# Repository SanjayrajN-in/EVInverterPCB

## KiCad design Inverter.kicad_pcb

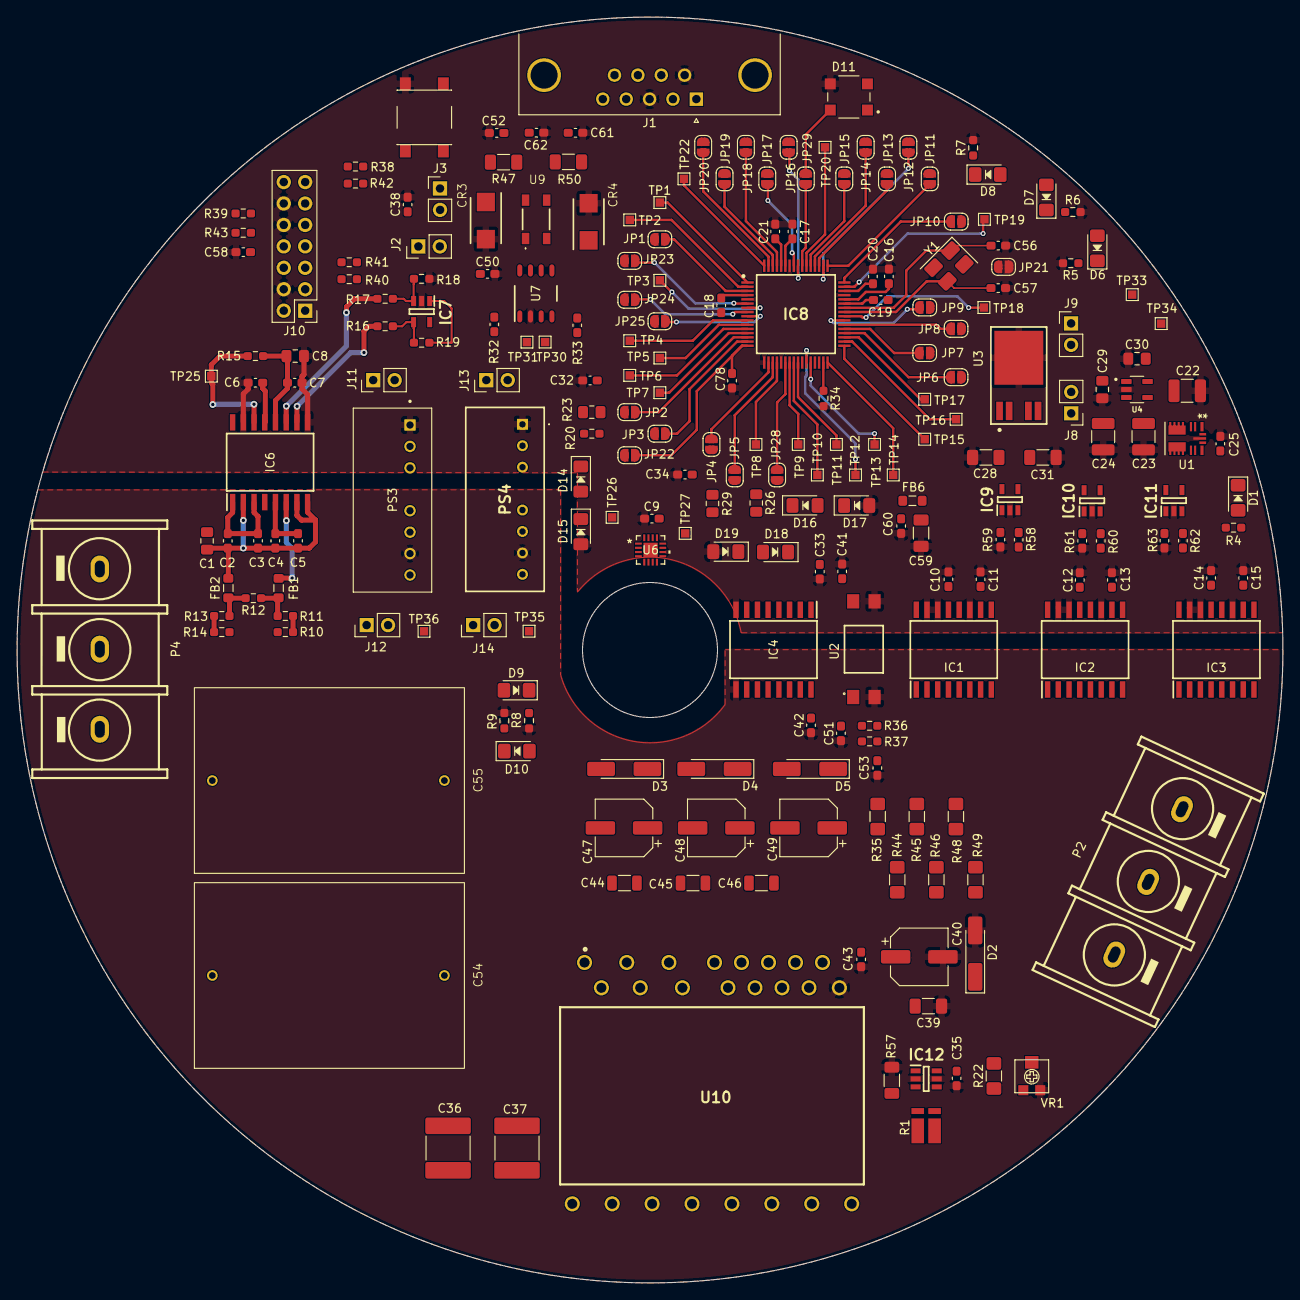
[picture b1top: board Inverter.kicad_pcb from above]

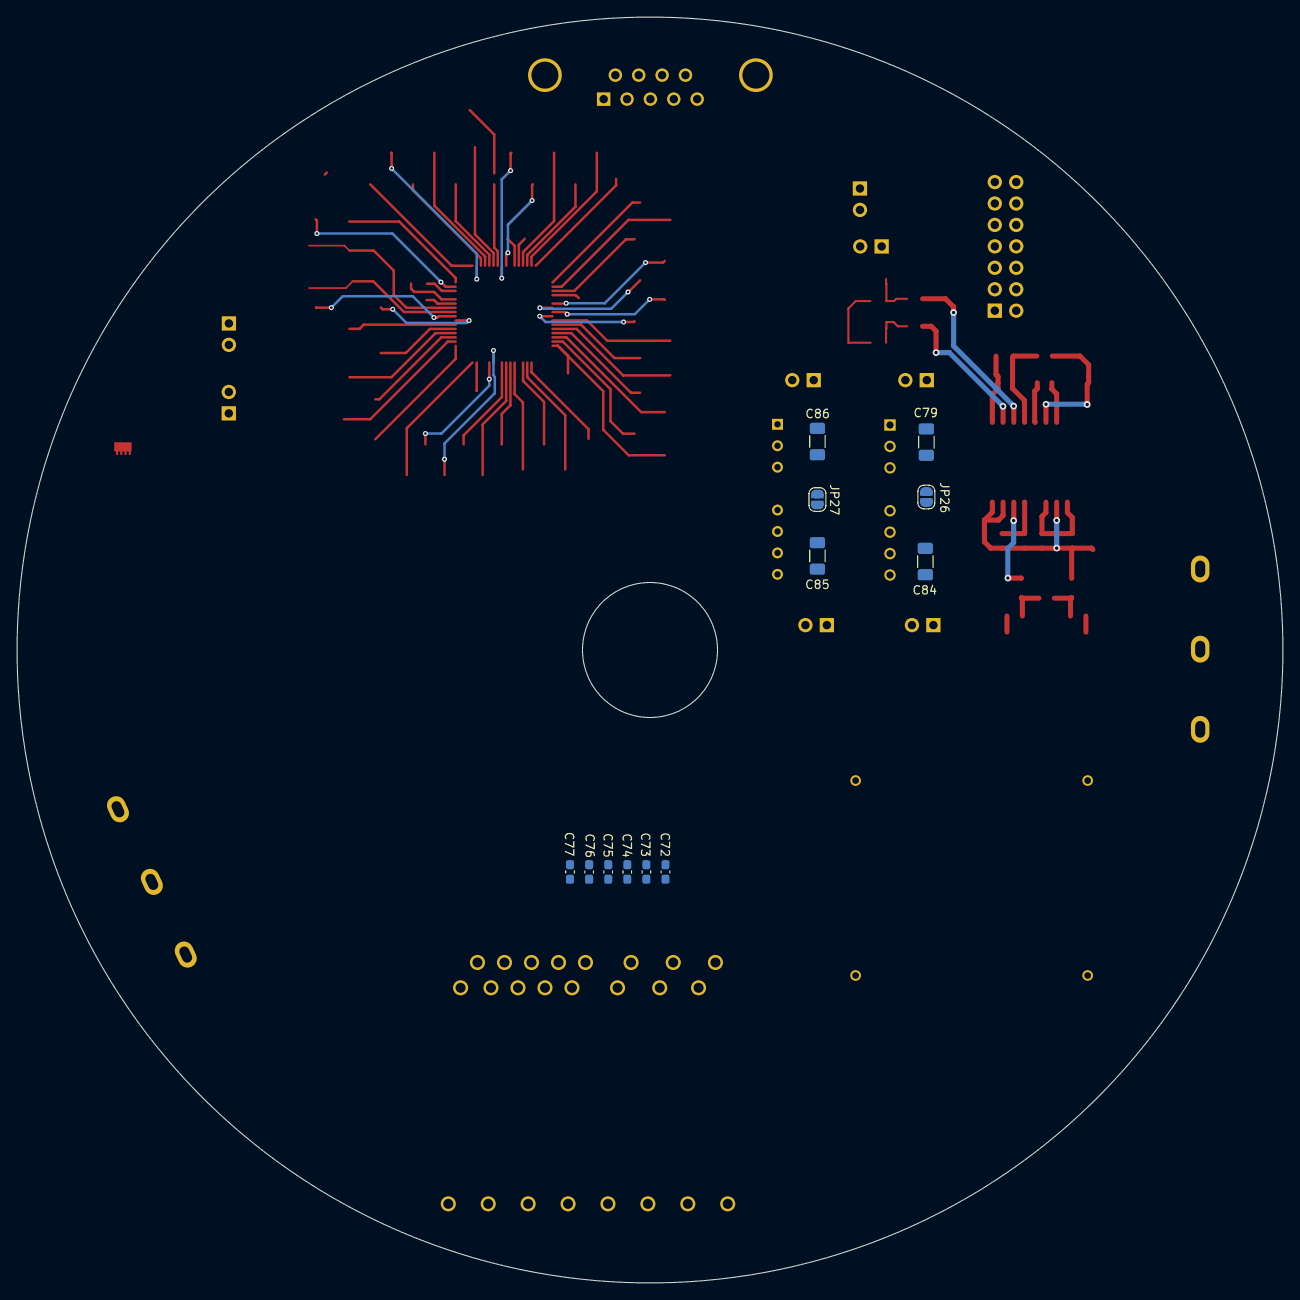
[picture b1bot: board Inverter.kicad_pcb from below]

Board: 2 copper layers, 150.0 x 150.0 mm, 236 parts (12 on the bottom side), 176 nets.

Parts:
C1, C8: 1u; C_0805_2012Metric_Pad1.18x1.45mm_HandSolder
C2, C5, C7: 1n; C_0603_1608Metric_Pad1.08x0.95mm_HandSolder
C3, C4, C6, C16, C17, C18, C19, C20, C21, C58, C60: 100n; C_0603_1608Metric_Pad1.08x0.95mm_HandSolder
C9, C25, C35: 1uF; C_0603_1608Metric_Pad1.08x0.95mm_HandSolder
C10, C12, C14, C43, C53: 1nF; C_0603_1608Metric_Pad1.08x0.95mm_HandSolder
C11, C41, C42, C51: 0.1uF; C_0603_1608Metric_Pad1.08x0.95mm_HandSolder
C13, C15, C38, C50, C52, C61, C62: 0.1u; C_0603_1608Metric_Pad1.08x0.95mm_HandSolder
C22: 4.7uF; C_1210_3225Metric_Pad1.33x2.70mm_HandSolder
C23, C24: 22uF; C_1210_3225Metric_Pad1.33x2.70mm_HandSolder
C28, C31, C84: 10uF; C_1206_3216Metric_Pad1.33x1.80mm_HandSolder
C29, C30: 10uF; C_0805_2012Metric_Pad1.18x1.45mm_HandSolder
C32, C33, C34, C72, C73, C74, C75, C76, C77: 100nF; C_0603_1608Metric_Pad1.08x0.95mm_HandSolder
C36, C37: 2.2u; C_2220_5750Metric_Pad1.97x5.40mm_HandSolder
C39: 1u; C_1206_3216Metric_Pad1.33x1.80mm_HandSolder
C40: 10u; CP_Elec_6.3x5.9
C44, C45, C46: 2.2uF; C_1206_3216Metric
C47, C48, C49: 100uF/25V; CP_Elec_6.3x5.9
C54, C55: 22u; FilmCap
C56, C57: 22pF; C_0603_1608Metric_Pad1.08x0.95mm_HandSolder
C59: 4.7u; C_1206_3216Metric_Pad1.33x1.80mm_HandSolder
C78: 2.2uF; C_0603_1608Metric_Pad1.08x0.95mm_HandSolder
C79, C85, C86: 47uF; C_1206_3216Metric_Pad1.33x1.80mm_HandSolder
CR3, CR4: SMBJ30CA; DIOM5436X244N
D1: RED_LED; LED_1206
D2, D3, D4, D5: 16V; D_MiniMELF_Handsoldering
D6, D7, D8, D9, D10: LED; LED_1206
D11: XL-5050RGBC-WS2812B; LED_XL-5050RGBC-WS2812B
D14, D15, D16, D17, D18, D19: D_Zener; D_1206
FB1, FB2, FB6: FerriteBead; L_0805_2012Metric_Pad1.05x1.20mm_HandSolder
IC1, IC2, IC3: ACS724LMATR-20AB-T; SOIC127P1030X265-16N
IC4: ISO7760FQDWQ1; SOIC127P1030X265-16N
IC6: AMC3311QDWERQ1; SOIC127P1030X265-16N
IC7, IC9, IC10, IC11: OPA388QDBVRQ1; SOT95P280X145-5N
IC8: F2800157QPMQ1; QFP50P1200X1200X160-64N
IC12: INA181A2QDBVRQ1; SOT95P280X145-6N
J1: Conn_01x09_Pin; DSUB-9_Pins_Horizontal_P2.77x2.84mm_EdgePinOffset4.94mm_Hou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
J2, J3, J8, J9, J11, J12, J13, J14: Conn_01x02_Pin; PinHeader_1x02_P2.54mm_Vertical
J10: Conn_02x07_Odd_Even; PinHeader_2x07_P2.54mm_Vertical
JP1, JP2, JP3, JP4, JP5, JP6, JP7, JP8, JP9, JP10, JP11, JP12, JP13, JP14, JP15, JP16, JP17, JP18, JP19, JP20, JP21, JP22, JP23, JP24, JP25, JP26, JP27, JP28, JP29: SolderJumper_2_Open; SolderJumper-2_P1.3mm_Open_RoundedPad1.0x1.5mm
P2, P4: WJ45C-B-3P
PS3: MCWI05-12S05; CONV_MCWI05-12S05
PS4: MCWI05-12S15; MCWI0512S15
R1: 0.0007; WSK1216
R4, R12, R34, R37, R38, R39, R40, R41, R42, R43: 10k; R_0603_1608Metric_Pad0.98x0.95mm_HandSolder
R5, R6, R7, R8, R9: 2.2k; R_0603_1608Metric_Pad0.98x0.95mm_HandSolder
R10, R14, R16, R17, R18, R19: 100k; R_0603_1608Metric_Pad0.98x0.95mm_HandSolder
R11, R13: 150k; R_0603_1608Metric_Pad0.98x0.95mm_HandSolder
R15: 47k; R_0603_1608Metric_Pad0.98x0.95mm_HandSolder
R20: 100; R_0603_1608Metric_Pad0.98x0.95mm_HandSolder
R22, R35, R44, R45, R46, R48, R49: R; R_1206
R23, R26, R29: 100; C_0805_2012Metric_Pad1.18x1.45mm_HandSolder
R32, R33: 50; C_0603_1608Metric_Pad1.08x0.95mm_HandSolder
R36: 220; R_0603_1608Metric_Pad0.98x0.95mm_HandSolder
R47, R50: 60; C_1206_3216Metric_Pad1.33x1.80mm_HandSolder
R57: 0R; R_1206_3216Metric_Pad1.30x1.75mm_HandSolder
R58, R60, R62: 10k; C_0603_1608Metric_Pad1.08x0.95mm_HandSolder
R59, R61, R63: 19.6k; C_0603_1608Metric_Pad1.08x0.95mm_HandSolder
SW1: SW_MEC_5E; PushButton
TP1, TP2, TP3, TP4, TP5, TP6, TP7, TP8, TP9, TP10, TP11, TP12, TP13, TP14, TP15, TP16, TP17, TP18, TP19, TP20, TP22, TP25, TP26, TP27, TP30, TP31, TP33, TP34, TP35, TP36: TestPoint; TestPoint_Pad_1.0x1.0mm
U1: TPSM33610S5QRDNRQ1
U2: VO617A-3X018T; SOIC254P1210X390-4N
U3: TPS78533QKVURQ1; TO114P998X235-6_5N-V
U4: TLV70012QDDCRQ1; SOT95P280X110-5N
U6: MA732GQ-P; QFN-16_MA732
U7: TCAN1042HGVDRQ1; D0008A_N
U9: ACT45C-110-2P-TL000
U10: IGCM15F60GA
VR1: EVM-3YSX50B53
Y1: Crystal_GND24; Crystal_SMD_EuroQuartz_MT-4Pin_3.2x2.5mm_HandSoldering

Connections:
+1V2: C16.1, C17.1, C18.1, D8.2 (A), IC8.4 (VDD_1), IC8.44 (VDD_2), IC8.59 (VDD_3), J9.1, TP33.1 (1_1)
+3.3V: C9.1, C19.1, C20.1, C21.1, C41.2, D7.2 (A), FB6.1, IC4.1 (VCC1), IC7.5 (V+), IC8.43 (VDDIO_1), IC8.46 (VREGENZ), IC8.60 (VDDIO_2), J3.1, J8.2, J10.5, R38.1, R39.1, R40.1, R41.1, R42.1, R43.2, TP34.1 (1_1), U6.13 (VDD)
+5V: C7.2, C8.2, C11.1, C13.1, C15.1, C23.1, C24.1, C28.2, D6.2 (A), D11.1 (VDD), IC1.10 (VCC), IC2.10 (VCC), IC3.10 (VCC), IC6.12 (VDD), J2.1, R15.1, U1.4 (VOUT), U1.9 (FB), U3.1 (EN), U3.2 (IN)
+5VA: C35.1, C42.2, D10.2 (A), IC4.16 (VCC2), IC12.6 (VS), J12.2, R37.1, TP36.1 (1_1)
+12V: C22.1, J1.9, J11.1, J13.1, R4.1, U1.2 (EN), U1.3 (VIN)
+15V: C39.1, C40.1, D2.1 (K), D9.2 (A), J14.2, TP35.1 (1_1), U10.13 (VDD)
+DCLink: C36.2, C37.1, C54.2, C55.1, P4.1, R10.1, U10.23
+INSense: IC12.3 (IN+), R1.3
-DCLink: C36.1, C37.2, C54.1, C55.2, P4.3, R1.1, R14.2, R57.1
-INSense: IC12.4 (IN-), R1.2
/Interface/VCC: C50.1, J2.2, U7.3 (VCC)
/Interface/VIO: C38.1, J3.2, U7.5 (VIO)
/Inverter_PowerStage/A: C72.1, R35.2, U10.7 (HIN(U))
/Inverter_PowerStage/B: C73.1, R44.2, U10.8 (HIN(V))
/Inverter_PowerStage/C: C74.1, R45.2, U10.9 (HIN(W))
/Inverter_PowerStage/D: C75.1, R46.2, U10.10 (LIN(U))
/Inverter_PowerStage/E: C76.1, R48.2, U10.11 (LIN(V))
/Inverter_PowerStage/F: C77.1, R49.2, U10.12 (LIN(W))
/Power_SM/PGOOD: D1.1 (K), U1.1 (PGOOD)
ADC_IU: C32.1, D14.2 (A), D15.1 (K), JP2.2 (B), R23.1
ADC_IV: C33.1, D16.2 (A), D17.1 (K), JP5.2 (B), R26.1
ADC_IW: C34.1, D18.2 (A), D19.1 (K), JP4.2 (B), R29.1
AD_REF: C59.1, C60.1, D14.1 (K), D16.1 (K), D18.1 (K), FB6.2, IC9.5 (V+), IC10.5 (V+), IC11.5 (V+), JP22.2 (B), JP28.2 (B)
CAN1RX: R33.2, TP30.1 (1_1), U7.4 (RXD)
CAN1TX: R32.2, TP31.1 (1_1), U7.1 (TXD)
CANH: C52.1, J1.7, R47.1, U9.4
CANL: C61.2, J1.2, R50.2, U9.3
CANSTB: IC8.31 (GPIO11), R34.1, U7.8 (STB)
DC_OUTN: IC6.10 (OUTN), R16.2
DC_OUTP: IC6.11 (OUTP), R17.2
DC_Sense: JP3.2 (B), R20.2
DIN_LED: D11.4 (DIN), JP29.1 (A)
EMU0: J10.13, R38.2
EMU1: J10.14, R39.2
GND: C6.2, C7.1, C8.1, C9.2, C10.2, C11.2, C12.2, C13.2, C14.2, C15.2, C16.2, C17.2, C18.2, C19.2, C20.2, C21.2, C22.2, C23.2, C24.2, C25.2, C28.1, C29.1, C30.1, C31.2, C32.2, C33.2, C34.2, C38.2, C41.1, C50.2, C52.2, C56.2, C57.1, C58.2, C59.2, C60.2, C61.1, C62.2, C78.2, C79.2, C86.1, CR3.2, CR4.2, D11.3 (GND), D15.2 (A), D17.2 (A), D19.2 (A), IC1.11 (NC_2), IC1.14 (NC_3), IC1.15 (GND), IC2.11 (NC_2), IC2.14 (NC_3), IC2.15 (GND), IC3.11 (NC_2), IC3.14 (NC_3), IC3.15 (GND), IC4.8 (GND1), IC6.9 (GND), IC6.15 (DCDC_GND), IC7.2 (V-), IC8.5 (VSS_1), IC8.17 (VREFLO), IC8.21 (VSSA), IC8.26 (VSS_2), IC8.45 (VSS_3), IC8.58 (VSS_4), IC9.2 (V-), IC10.2 (V-), IC11.2 (V-), J1.3, J1.6, J10.4, J10.10, J10.12, JP21.1 (A), JP26.2 (B), JP27.2 (B), PS3.1 (-VIN), PS4.1 (-VIN), R5.2, R6.2, R7.2, R18.2, R34.2, R59.2, R61.2, R63.2, SW1.2, U1.10 (GND), U1.11 (MODE/SYNC), U2.3, U3.3 (GND), U4.2 (GND), U6.8 (GND), U6.10 (TEST), U6.17 (PAD), U7.2 (GND)
GND1: C35.2, C39.2, C40.2, C42.1, C43.2, C51.2, C53.2, C72.2, C73.2, C74.2, C75.2, C76.2, C77.2, C84.2, C85.2, D2.2 (A), IC4.9 (GND2), IC12.2 (GND), IC12.5 (REF), PS3.7 (-VOUT), PS4.7 (-VOUT), R8.2, R9.2, R57.2, U2.2, U10.16 (VSS), VR1.P$3
ITRIP: C43.1, R22.2, U10.15 (ITRIP), VR1.P$1, VR1.P$2
ITRIPOUT: IC12.1 (OUT), R22.1
Iu_In: IC1.1 (IP+_1), IC1.2 (IP+_2), IC1.3 (IP+_3), IC1.4 (IP+_4), U10.22 (U)
Iu_Out: IC1.5 (IP-_1), IC1.6 (IP-_2), IC1.7 (IP-_3), IC1.8 (IP-_4), P2.1
Iu_div: IC9.3 (+IN), R58.2, R59.1
Iu_sense: IC1.12 (VIOUT), R58.1
Iv_In: IC2.1 (IP+_1), IC2.2 (IP+_2), IC2.3 (IP+_3), IC2.4 (IP+_4), U10.21 (V)
Iv_Out: IC2.5 (IP-_1), IC2.6 (IP-_2), IC2.7 (IP-_3), IC2.8 (IP-_4), P2.2
Iv_div: IC10.3 (+IN), R60.2, R61.1
Iv_sense: IC2.12 (VIOUT), R60.1
Iw_In: IC3.1 (IP+_1), IC3.2 (IP+_2), IC3.3 (IP+_3), IC3.4 (IP+_4), U10.20 (W)
Iw_Out: IC3.5 (IP-_1), IC3.6 (IP-_2), IC3.7 (IP-_3), IC3.8 (IP-_4), P2.3
Iw_div: IC11.3 (+IN), R62.2, R63.1
Iw_sense: IC3.12 (VIOUT), R62.1
JTAG_SEL: C58.1, J10.8, R43.1
unnamed: C62.1, R47.2, R50.1
unnamed: D1.2 (A), R4.2
unnamed: D6.1 (K), R5.1
unnamed: D7.1 (K), R6.1
unnamed: D8.1 (K), R7.1
unnamed: D9.1 (K), R8.1
unnamed: D10.1 (K), R9.1
unnamed: FB1.1, R11.2, R12.1
unnamed: FB2.1, R12.2, R13.1
unnamed: C10.1, IC1.13 (FILTER)
unnamed: C12.1, IC2.13 (FILTER)
unnamed: C14.1, IC3.13 (FILTER)
unnamed: IC4.15 (OUTA), R49.1
unnamed: IC4.14 (OUTB), R48.1
unnamed: IC4.13 (OUTC), R46.1
unnamed: IC4.12 (OUTD), R45.1
unnamed: IC4.11 (OUTE), R44.1
unnamed: IC4.10 (OUTF), R35.1
unnamed: C1.1, C2.1, C3.1, C4.1, C5.2, FB2.2, IC6.2 (DCDC_HGND), IC6.7 (HGND_1), IC6.8 (HGND_2)
unnamed: C6.1, IC6.13 (LDO_OUT), IC6.16 (DCDC_IN)
unnamed: C1.2, C2.2, C3.2, IC6.1 (DCDC_OUT), IC6.3 (HLDO_IN)
unnamed: IC6.14 (DIAG), R15.2, TP25.1 (1_1)
unnamed: C4.2, C5.1, IC6.5 (HLDO_OUT)
unnamed: FB1.2, IC6.6 (IN)
unnamed: IC7.3 (+IN), R17.1, R18.1
unnamed: IC7.4 (-IN), R16.1, R19.1
unnamed: IC7.1 (OUT), R19.2, R20.1
unnamed: IC8.15 (A0/C15/CMP1_DACL), JP3.1 (A)
unnamed: IC8.14 (A1), JP2.1 (A)
unnamed: IC8.9 (A2/C9GPIO224), JP25.2 (B)
unnamed: IC8.8 (A3/C5GPIO242), JP24.2 (B)
unnamed: IC8.23 (A4/C14), TP9.1 (1_1)
unnamed: IC8.13 (A5/C2), TP7.1 (1_1)
unnamed: IC8.6 (A6GPIO228), JP23.2 (B)
unnamed: IC8.19 (A7/C3), JP5.1 (A)
unnamed: IC8.20 (A8/C11), TP8.1 (1_1)
unnamed: IC8.25 (A10/C10GPIO230), TP11.1 (1_1)
unnamed: IC8.12 (A11/C0), TP6.1 (1_1)
unnamed: IC8.18 (A12/C1), JP4.1 (A)
unnamed: IC8.10 (A15/C7), TP4.1 (1_1)
unnamed: IC8.2 (A16/C16GPIO28), TP2.1 (1_1)
unnamed: IC8.27 (A17/C17GPIO20), TP12.1 (1_1)
unnamed: IC8.28 (A18/C18GPIO21), TP13.1 (1_1)
unnamed: IC8.29 (A19/C19GPIO13), R32.1
unnamed: IC8.30 (A20/C20GPIO12), R33.1
unnamed: IC8.11 (C4/A14), TP5.1 (1_1)
unnamed: IC8.7 (C6GPIO226), TP3.1 (1_1)
unnamed: IC8.24 (C8/A9GPIO227), TP10.1 (1_1)
unnamed: IC8.52 (GPIO0), JP14.2 (B)
unnamed: IC8.51 (GPIO1), JP13.2 (B)
unnamed: IC8.50 (GPIO2), JP12.2 (B)
unnamed: IC8.49 (GPIO3), JP11.2 (B)
unnamed: IC8.48 (GPIO4), JP10.1 (A)
unnamed: IC8.61 (GPIO5), JP18.2 (B)
unnamed: IC8.64 (GPIO6), TP22.1 (1_1)
unnamed: IC8.57 (GPIO7), JP17.2 (B)
unnamed: IC8.47 (GPIO8), TP19.1 (1_1)
unnamed: IC8.62 (GPIO9), JP19.2 (B)
unnamed: IC8.63 (GPIO10), JP20.2 (B)
unnamed: IC8.33 (GPIO16), TP15.1 (1_1)
unnamed: IC8.34 (GPIO17), TP16.1 (1_1)
unnamed: IC8.56 (GPIO22), JP16.2 (B)
unnamed: IC8.54 (GPIO23), TP20.1 (1_1)
unnamed: IC8.35 (GPIO24), TP17.1 (1_1)
unnamed: IC8.1 (GPIO29), TP1.1 (1_1)
unnamed: IC8.40 (GPIO32), TP18.1 (1_1)
unnamed: IC8.32 (GPIO33), TP14.1 (1_1)
unnamed: IC8.39 (GPIO35/TDI), JP9.2 (B)
unnamed: IC8.37 (GPIO37/TDO), JP7.2 (B)
unnamed: IC8.53 (GPIO40), JP15.2 (B)
unnamed: IC8.55 (GPIO41), JP29.2 (B)
unnamed: IC8.36 (TCK), JP6.2 (B)
unnamed: IC8.38 (TMS), JP8.1 (A)
unnamed: IC8.22 (VDDA), JP28.1 (A)
unnamed: IC8.3 (XRSN), JP1.2 (B)
unnamed: IC9.1 (OUT), IC9.4 (-IN), R23.2
unnamed: IC10.1 (OUT), IC10.4 (-IN), R26.2
unnamed: IC11.1 (OUT), IC11.4 (-IN), R29.2
unnamed: C29.2, C31.1, J8.1, U3.4 (OUT), U4.1 (IN), U4.3 (EN)
unnamed: C30.2, J9.2, U4.5 (OUT)
unnamed: C79.1, J11.2, PS3.2 (+VIN)
unnamed: C84.1, J12.1, PS3.6 (+VOUT)
unnamed: C86.2, J13.2, PS4.2 (+VIN)
unnamed: C85.1, J14.1, PS4.6 (+VOUT)
unnamed: JP21.2 (B), Y1.2 (G), Y1.4 (G)
unnamed: JP26.1 (A), PS3.3 (REMOTE_ON/OFF)
unnamed: JP27.1 (A), PS4.3 (REMOTE_ON/OFF)
unnamed: R10.2, R11.1
unnamed: R13.2, R14.1
unnamed: C25.1, U1.8 (VCC)
unnamed: TP26.1 (1_1), U6.16 (MGH)
unnamed: TP27.1 (1_1), U6.11 (MGL)
unnamed: CR3.1, U7.7 (CANH), U9.1
unnamed: CR4.1, U7.6 (CANL), U9.2
unnamed: R1.4, U10.17 (NW), U10.18 (NV), U10.19 (NU)
PWMA1: IC4.7 (INF), JP14.1 (A)
PWMA2: IC4.4 (INC), JP13.1 (A)
PWMB1: IC4.6 (INE), JP12.1 (A)
PWMB2: IC4.3 (INB), JP11.1 (A)
PWMC1: IC4.5 (IND), JP10.2 (B)
PWMC2: IC4.2 (INA), JP18.1 (A)
SPIACLK: JP19.1 (A), U6.12 (SCLK)
SPIACS: JP16.1 (A), U6.5 (CS)
SPIAMISO: JP20.1 (A), U6.7 (MISO)
SPIAMOSI: JP17.1 (A), U6.4 (MOSI)
TCK: J10.11, JP6.1 (A), R42.2
TDI: J10.3, JP9.1 (A), R41.2
TDO: J10.7, JP7.1 (A)
TMS: J10.1, JP8.2 (B), R40.2
VB(U): C44.2, C47.1, D3.1 (K), U10.2 (VB(U))
VB(V): C45.2, C48.1, D4.1 (K), U10.4 (VB(V))
VB(W): C46.1, C49.1, D5.1 (K), U10.6 (VB(W))
VFO: C53.1, R36.1, R37.2, U10.14 (VFO)
VFO(I): C51.1, R36.2, U2.1
VFO(O): JP15.1 (A), U2.4
VREFHI: C78.1, IC8.16 (VREFHI), JP22.1 (A)
VS(U): C44.1, C47.2, D3.2 (A), U10.1 (VS(U))
VS(V): C45.1, C48.2, D4.2 (A), U10.3 (VS(V))
VS(W): C46.2, C49.2, D5.2 (A), U10.5 (VS(W))
X1: C56.1, IC8.42 (GPIO19X1), Y1.1
X2: C57.2, IC8.41 (GPIO18X2), Y1.3
XRSn: J10.2, JP1.1 (A), SW1.3 (K)
eQEPA: JP25.1 (A), U6.2 (A)
eQEPB: JP23.1 (A), U6.6 (B)
eQEPZ: JP24.1 (A), U6.3 (Z)
